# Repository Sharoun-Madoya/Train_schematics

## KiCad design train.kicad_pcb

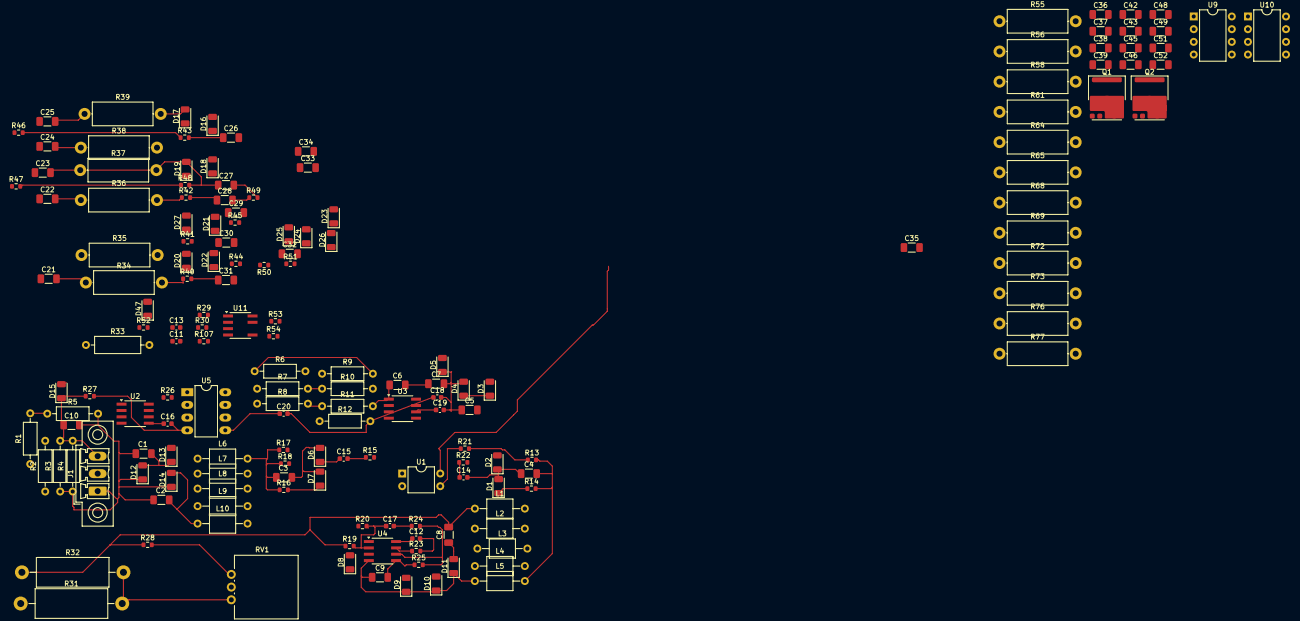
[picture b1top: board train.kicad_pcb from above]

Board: 2 copper layers, 164 parts (0 on the bottom side), 68 nets.

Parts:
C1, C2, C3, C4, C5, C6, C7, C8, C9, C10, C21, C22, C23, C24, C25, C26, C27, C28, C29, C30, C31, C32, C33, C34, C35, C36, C37, C38, C39, C42, C43, C45, C46, C48, C49, C51, C52: C; C_1206_3216Metric_Pad1.33x1.80mm_HandSolder
C11, C12, C13, C14, C15, C16, C17, C18, C19, C20: C; C_0603_1608Metric
D1, D2, D3, D4, D5, D6, D7, D8, D9, D10, D11, D12, D13, D14, D15: D; D_1206_3216Metric
D16, D17, D18, D19, D20, D21, D22, D23, D24, D25, D26, D27, D47: IR26-21C_L110_TR8; LED_1206_3216Metric
J1: Conn_01x03_Pin; PhoenixContact_MCV_1,5_3-GF-3.5_1x03_P3.50mm_Vertical_Threa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
L1, L2, L3, L4, L5, L6, L7, L8, L9, L10: L; L_Axial_L5.0mm_D3.6mm_P10.00mm_Horizontal_Murata_BL01RN1A2A2
Q1, Q2: GS66508B; GaN_Systems_GaNPX-4_7x8.4mm
R1, R2, R3, R4, R5, R6, R7, R8, R9, R10, R11, R12: R; R_Axial_DIN0207_L6.3mm_D2.5mm_P10.16mm_Horizontal
R13, R14, R15, R16, R17, R18, R19, R20, R21, R22, R23, R24, R25, R26, R27, R28, R29, R30, R40, R41, R42, R43, R44, R45, R46, R47, R48, R49, R50, R51, R52, R53, R54, R107: R; R_0603_1608Metric
R31, R32: R; R_Axial_DIN0614_L14.3mm_D5.7mm_P20.32mm_Horizontal
R33: R; R_Axial_DIN0309_L9.0mm_D3.2mm_P12.70mm_Horizontal
R34, R35, R36, R37, R38, R39, R55, R56, R58, R61, R64, R65, R68, R69, R72, R73, R76, R77: R; R_Axial_DIN0414_L11.9mm_D4.5mm_P15.24mm_Horizontal
RV1: R_Potentiometer; Potentiometer_Vishay_148-149_Single_Vertical
U1: EL817; DIP-4_W7.62mm
U2, U3, U4: AD8606ARM; PowerIntegrations_SO-8
U5: L272M; DIP-8_W7.62mm_LongPads
U9, U10: LTC1151CN8; DIP-8_W7.62mm
U11: LNK302D; PowerIntegrations_SO-8B

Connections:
/page2/Untitled Sheet page3/Untitled Sheet page4/gnd: U9.1, U9.7, U9.8 (V+), U10.3 (+), U10.4 (V-), U10.8 (V+)
unnamed: C1.2, R4.1
unnamed: C3.1, R17.2
unnamed: C3.2, R16.2, R18.2
unnamed: C4.2, R13.1, R14.2
unnamed: C6.2, C7.1
unnamed: C11.2, R107.1
unnamed: C12.1, U4.7
unnamed: C12.2, R23.1
unnamed: C14.1, R22.1
unnamed: C16.2, R27.1
unnamed: C17.2, R24.1
unnamed: C18.1, C20.2
unnamed: C21.2, R34.1
unnamed: C28.1, R49.1
unnamed: C28.2, R42.1
unnamed: C37.2, R56.1
unnamed: C38.2, R58.1
unnamed: C42.2, R64.1
unnamed: C45.2, R68.1
unnamed: C48.2, R72.1
unnamed: C51.2, R76.1
unnamed: C4.1, D1.2 (A), D2.1 (K)
unnamed: C14.2, D1.1 (K)
unnamed: C7.2, D4.2 (A)
unnamed: D6.2 (A), R15.1
unnamed: C15.1, D6.1 (K)
unnamed: C15.2, D7.2 (A)
unnamed: D7.1 (K), R16.1
unnamed: C8.2, D8.1 (K), L1.2, R19.1, R28.1, R32.1
unnamed: C8.1, D11.2 (A)
unnamed: D12.2 (A), R5.2, R27.2
unnamed: C25.2, D17.2 (A), R39.1
unnamed: C11.1, C13.1, D47.2 (A), R33.2
unnamed: C13.2, D47.1 (K), R29.1, R52.2
unnamed: Q1.3 (G), Q1.4 (SS)
unnamed: Q2.3 (G), Q2.4 (SS)
unnamed: R1.2, R3.1
unnamed: R2.2, R5.1
unnamed: R6.1, R9.2
unnamed: R7.2, R10.1
unnamed: R8.2, R11.1
unnamed: R13.2, R21.2
unnamed: R21.1, U1.3
unnamed: R24.2, R25.1
unnamed: R28.2, RV1.3
unnamed: R31.1, RV1.1
unnamed: R31.2, R32.2
unnamed: R34.2, R40.1
unnamed: R36.1, R42.2
unnamed: R43.1, R46.2
unnamed: C9.1, U4.3 (+)
unnamed: C17.1, R19.2, R20.2, U4.2 (-)
unnamed: R25.2, U4.5 (+), U4.6 (-)
unnamed: R23.2, U4.8 (V+)
unnamed: C20.1, R12.2, U5.5 (-)
unnamed: U11.5 (S), U11.7 (S), U11.8 (S)
R17: L6.2, R18.1
S4: C1.1, C10.1, C10.2, C16.1, D12.1 (K), D14.1 (K), D14.2 (A), D15.1 (K), J1.1, J1.3, L10.1, R3.2, R4.2, U2.5 (+), U5.4 (V-)
f2: C26.2, R43.2
f5: C26.1, C27.1, R47.2, R48.1, R48.2, R49.2
f6: C22.2, R36.2
f7: C31.1, R40.2
gnd: C22.1, C24.1, C36.1, C39.1, C43.1, C46.1, C49.1, C52.1, D8.2 (A), R1.1
in: C36.2, C39.2, C43.2, C46.2, C49.2, C52.2, R2.1, R33.1, R47.1, R52.1, R55.1, R61.1, R65.1, R69.1, R73.1, R77.1
l2: C6.1, C18.2, C19.2, D3.1 (K), D4.1 (K), U3.6 (-)
li3: D9.1 (K), D10.1 (K), D11.1 (K), U4.4 (V-)
u3_1: R11.2, U3.1

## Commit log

2025-01-23 :tada: Train schematics Uploaded
